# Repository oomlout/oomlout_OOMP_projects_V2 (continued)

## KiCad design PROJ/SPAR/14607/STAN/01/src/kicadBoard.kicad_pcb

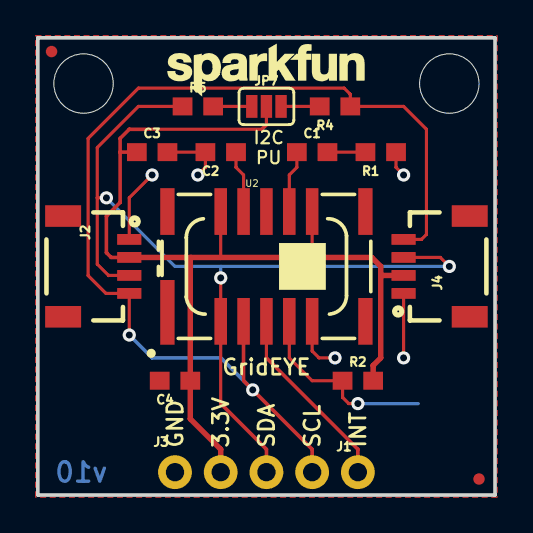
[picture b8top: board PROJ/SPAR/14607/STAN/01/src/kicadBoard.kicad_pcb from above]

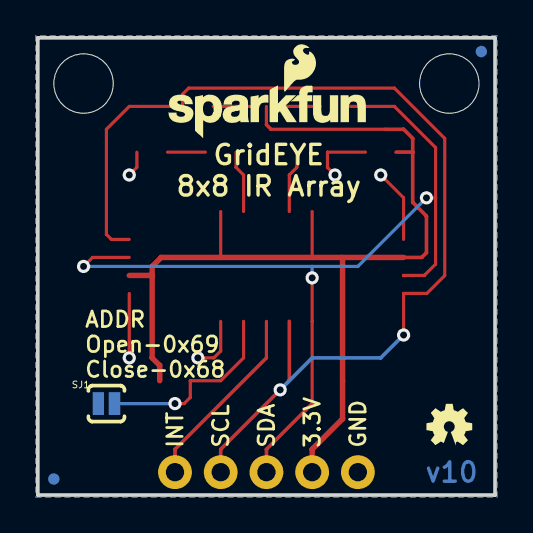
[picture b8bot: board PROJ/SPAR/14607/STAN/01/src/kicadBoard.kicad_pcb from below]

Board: 2 copper layers, 25.4 x 25.4 mm, 26 parts (5 on the bottom side), 11 nets.

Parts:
C1: 1.0uF; 0603
C2: 2.2uF; 0603
C3: 10uF; 0603
C4: 0.1uF; 0603
FRAME1: FRAME-LETTER; CREATIVE_COMMONS
J1: 1X01_NO_SILK
J2, J4: SMD; 1X04_1MM_RA
J3: PTH; 1X04_NO_SILK
JP1, JP2, JP5, JP6: FIDUCIALUFIDUCIAL; MICRO-FIDUCIAL
JP3, JP4: STAND-OFF
JP7: SMT-JUMPER_3_2-NC_PASTE_SILK
LOGO1: OSHW-LOGOMINI; OSHW-LOGO-MINI
LOGO2: REVISION
R1: 20; 0603
R2: 10k; 0603
R4, R5: 4.7k; 0603
SJ1: SJ_2S-NO
U2: GRIDEYE; GRIDEYE-AMG88
U$1: SFE_LOGO_NAME.1_INCH; SFE_LOGO_NAME_.1
U$2: SFE_LOGO_NAME_FLAME.1_INCH; SFE_LOGO_NAME_FLAME_.1

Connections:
3.3V: C3.1, C4.1, J2.2, J3.2, J4.2, JP7.2, R2.2, U2.9, U2.13
ADDR: R2.1, SJ1.2, U2.5
GND: C2.2, C3.2, C4.2, J2.1, J3.1, J4.1, R1.1, SJ1.1, U2.6
INT: J1.1, U2.4
unnamed: JP7.1, R5.2
unnamed: JP7.3, R4.2
unnamed: C2.1, U2.12
unnamed: C1.1, U2.10
unnamed: C1.2, R1.2
SCL: J2.4, J3.4, J4.4, R4.1, U2.3
SDA: J2.3, J3.3, J4.3, R5.1, U2.2
